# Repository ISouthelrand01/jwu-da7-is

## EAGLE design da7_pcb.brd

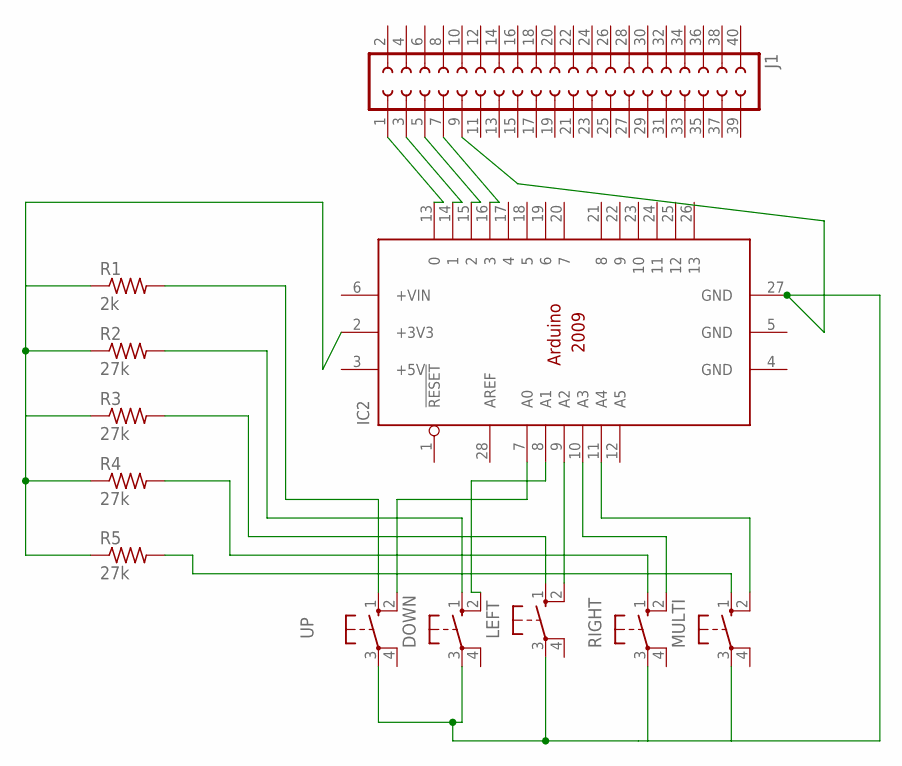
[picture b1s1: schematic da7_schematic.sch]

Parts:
DOWN: 10-XX; B3F-10XX
IC2: ARDUINO2009_10; ARDUINO2009
J1: SOCKET-40V; S40V
LEFT: 10-XX; B3F-10XX
MULTI: 10-XX; B3F-10XX
R1: 2k; 0204/7
R2, R3, R4, R5: 27k; 0204/7
RIGHT: 10-XX; B3F-10XX
UP: 10-XX; B3F-10XX

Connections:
+5V: IC2.3 (+5V)
GND: IC2.4 (GND), IC2.5 (GND)
unnamed: IC2.13 (0), J1.1
unnamed: IC2.14 (1), J1.3
unnamed: IC2.15 (2), J1.5
unnamed: IC2.16 (3), J1.7
unnamed: IC2.27 (GND), J1.9
unnamed: R1.2, UP.1 (S)
unnamed: DOWN.1 (S), R2.2
unnamed: LEFT.1 (S), R3.2
unnamed: R4.2, RIGHT.1 (S)
unnamed: MULTI.1 (S), R5.2
unnamed: IC2.2 (+3V3), R1.1, R2.1, R3.1, R4.1, R5.1
unnamed: IC2.7 (A0), UP.2 (S1)
unnamed: DOWN.2 (S1), IC2.8 (A1)
unnamed: IC2.9 (A2), LEFT.2 (S1)
unnamed: IC2.10 (A3), RIGHT.2 (S1)
unnamed: IC2.11 (A4), MULTI.2 (S1)
unnamed: DOWN.3, LEFT.3, MULTI.3, RIGHT.3, UP.3

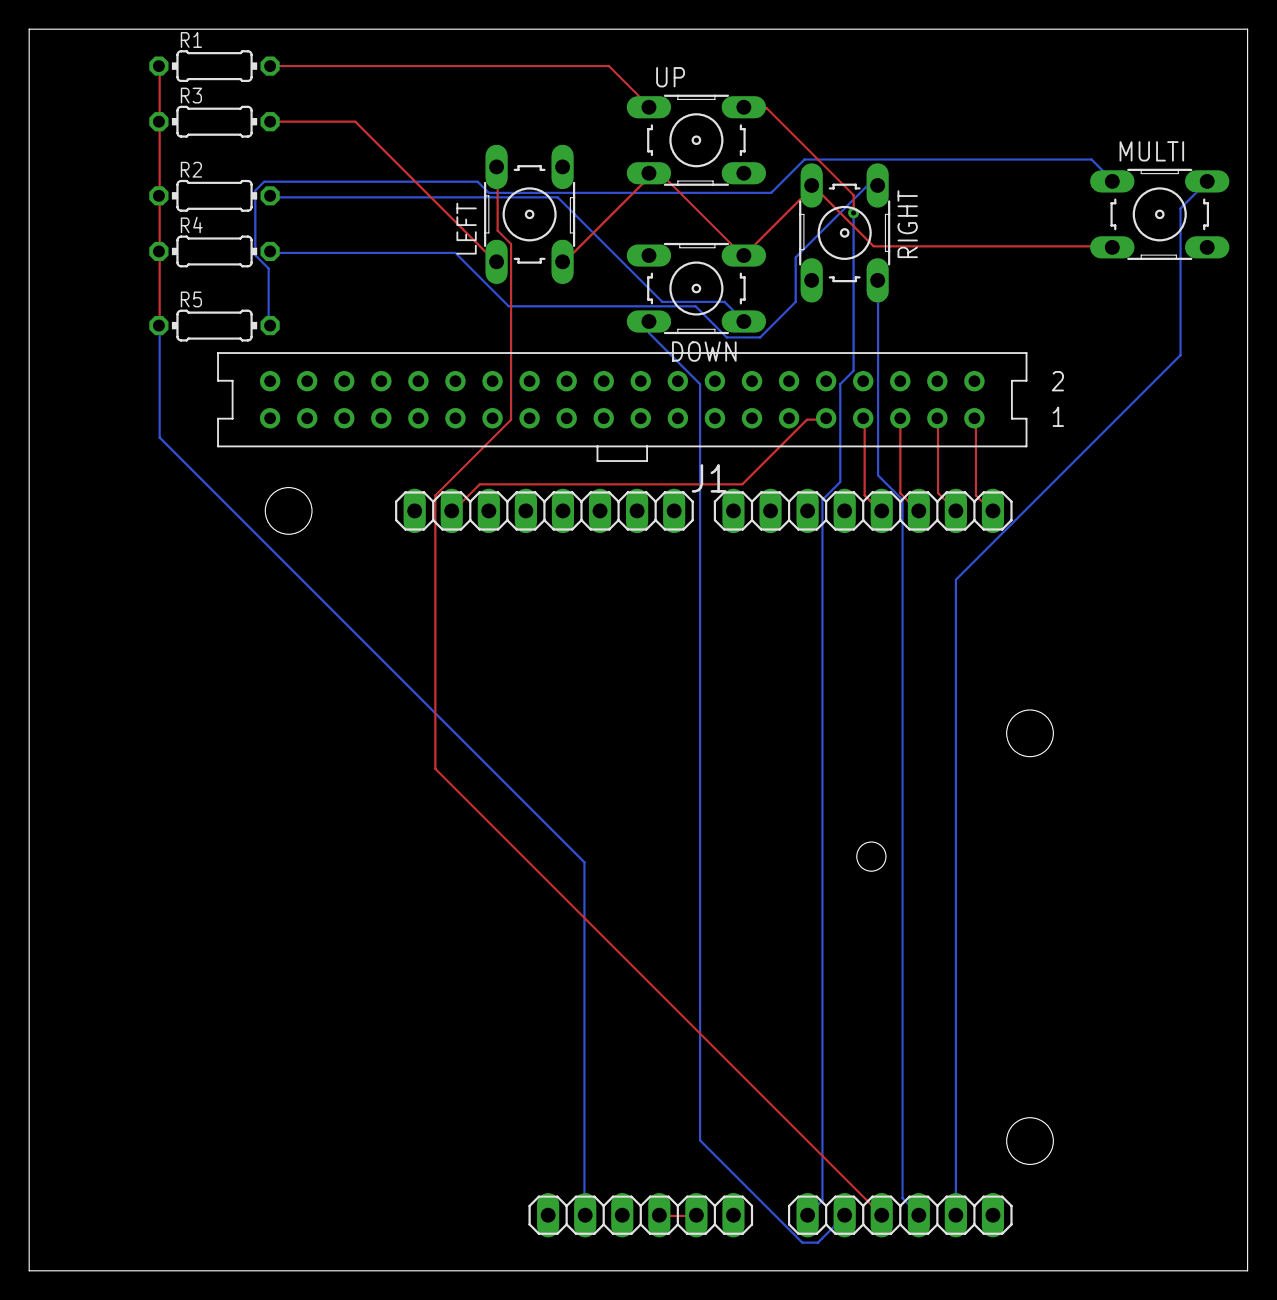
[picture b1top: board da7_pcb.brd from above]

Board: 2 copper layers, 83.5 x 85.1 mm, 12 parts (0 on the bottom side), 18 nets.
